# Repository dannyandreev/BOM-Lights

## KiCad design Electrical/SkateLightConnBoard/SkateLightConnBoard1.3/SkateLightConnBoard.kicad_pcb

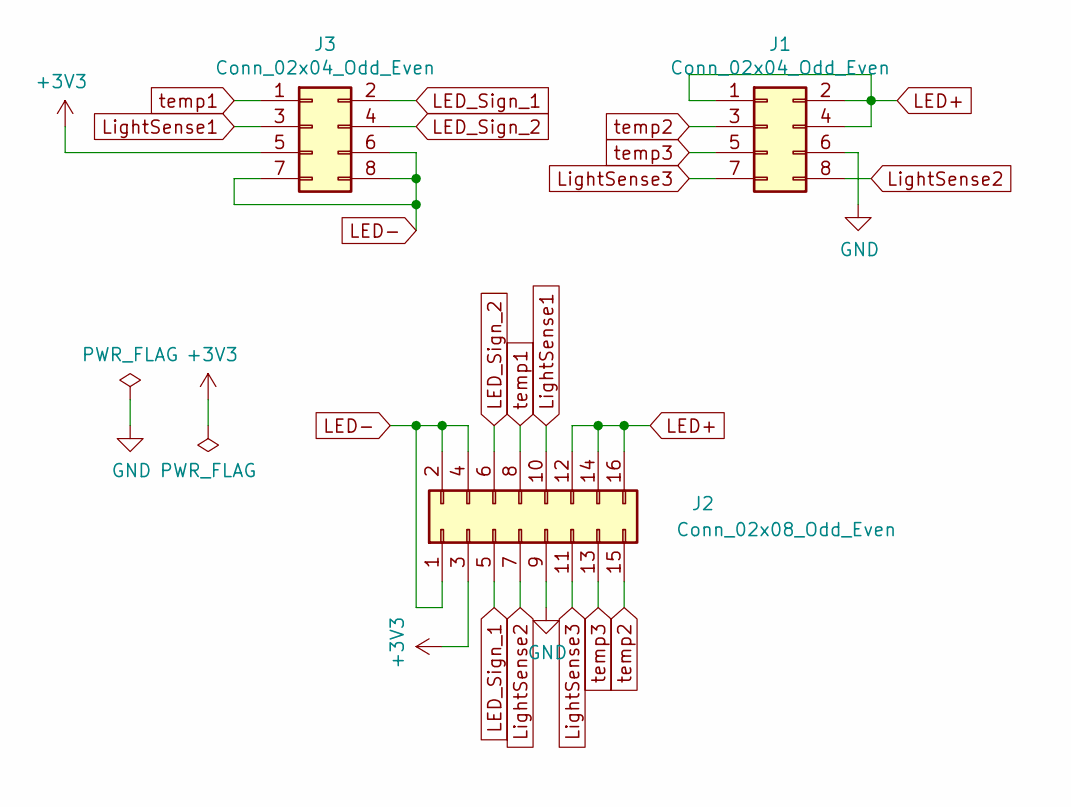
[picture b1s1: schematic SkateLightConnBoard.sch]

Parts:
J1, J3: Conn_02x04_Odd_Even; Conn_2x4_0.05in
J2: Conn_02x08_Odd_Even; Conn_2x8_0.05in

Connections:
+3V3: J2.3, J3.5
GND: J1.6, J2.9
LED+: J1.1, J1.2, J1.4, J2.12, J2.14, J2.16
LED-: J2.1, J2.2, J2.4, J3.6, J3.7, J3.8
LED_Sign_1: J2.5, J3.2
LED_Sign_2: J2.6, J3.4
LightSense1: J2.10, J3.3
LightSense2: J1.8, J2.7
LightSense3: J1.7, J2.11
temp1: J2.8, J3.1
temp2: J1.3, J2.15
temp3: J1.5, J2.13

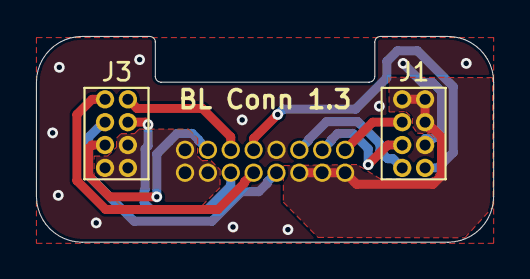
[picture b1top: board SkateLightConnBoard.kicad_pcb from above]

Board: 2 copper layers, 25.4 x 11.4 mm, 3 parts (1 on the bottom side), 12 nets.

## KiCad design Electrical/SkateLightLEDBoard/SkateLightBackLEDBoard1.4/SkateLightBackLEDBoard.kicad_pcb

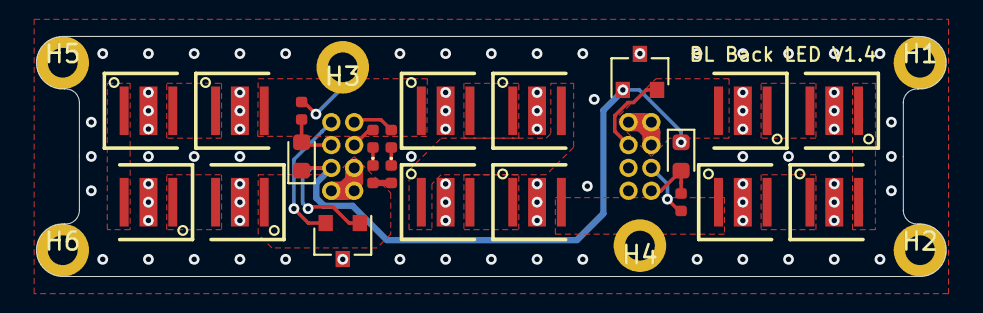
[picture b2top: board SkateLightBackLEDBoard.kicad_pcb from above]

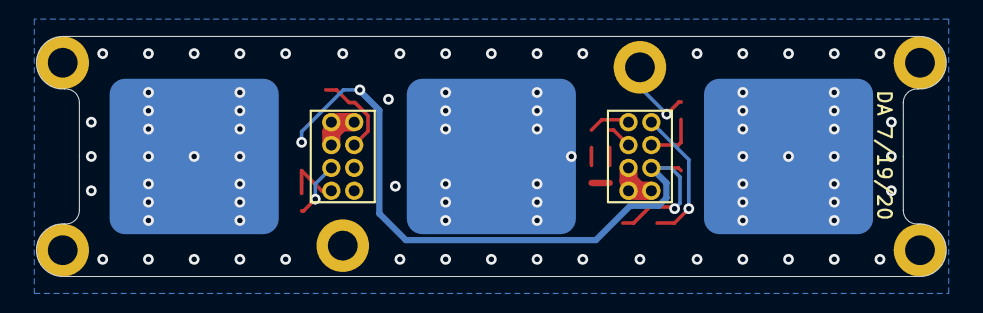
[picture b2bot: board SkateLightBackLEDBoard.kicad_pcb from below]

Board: 2 copper layers, 50.5 x 13.3 mm, 33 parts (5 on the bottom side), 23 nets.

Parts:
D1, D2, D3, D4, D5, D6, D7, D8, D9, D10, D11, D12: LED_PAD; SST-10-DR-B90-G660
D13: LEDR; D_0402_1005Metric
D14: LEDG; D_0402_1005Metric
H1, H2, H3, H4, H5, H6: MountingHole_Pad; MH_0-80_Screw_Grounded
HS1, HS2, HS3: Heatsink_Pad; BomLightBackLEDHeatsink
J1, J2: Conn_02x04_Odd_Even; Conn_2x4_0.05in
Q1, Q2: Q_Photo_NPN; D_0603_1608Metric
R1, R2: 10k 5%; R_0402_1005Metric
R3: 2k7 5%; R_0402_1005Metric
R4: 390 5%; R_0402_1005Metric
U1, U2: MCP9700AT-E_TT; SOT-23

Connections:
+3V3: J1.6, Q1.1, Q2.1, U1.1, U2.1
GND: D1.3, D2.3, D3.3, D4.3, D5.3, D6.3, D7.3, D8.3, D9.3, D10.3, D11.3, D12.3, H1.1, H2.1, H3.1, H4.1, H5.1, H6.1, HS1.1, HS2.1, HS3.1, J2.5, R1.2, R2.2, R3.2, R4.2, U1.3, U2.3
LED+: D12.2, J2.1, J2.2, J2.3
LED-: D1.1, J1.5, J1.7, J1.8
LED_Sign_1: D13.2, J1.1
LED_Sign_2: D14.2, J1.3
LightSense1: J1.4, Q1.2, R1.1
LightSense2: J2.7, Q2.2, R2.1
unnamed: D1.2, D2.1
unnamed: D2.2, D3.1
unnamed: D3.2, D4.1
unnamed: D4.2, D5.1
unnamed: D5.2, D6.1
unnamed: D6.2, D7.1
unnamed: D7.2, D8.1
unnamed: D8.2, D9.1
unnamed: D9.2, D10.1
unnamed: D10.2, D11.1
unnamed: D11.2, D12.1
unnamed: D13.1, R3.1
unnamed: D14.1, R4.1
Temp1: J1.2, U1.2
Temp2: J2.4, U2.2

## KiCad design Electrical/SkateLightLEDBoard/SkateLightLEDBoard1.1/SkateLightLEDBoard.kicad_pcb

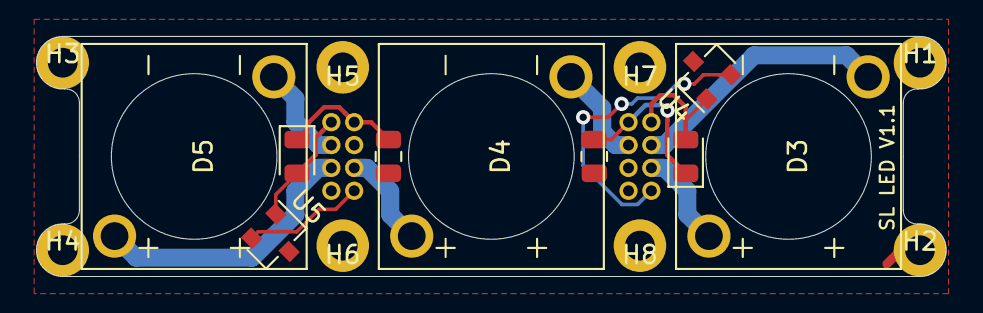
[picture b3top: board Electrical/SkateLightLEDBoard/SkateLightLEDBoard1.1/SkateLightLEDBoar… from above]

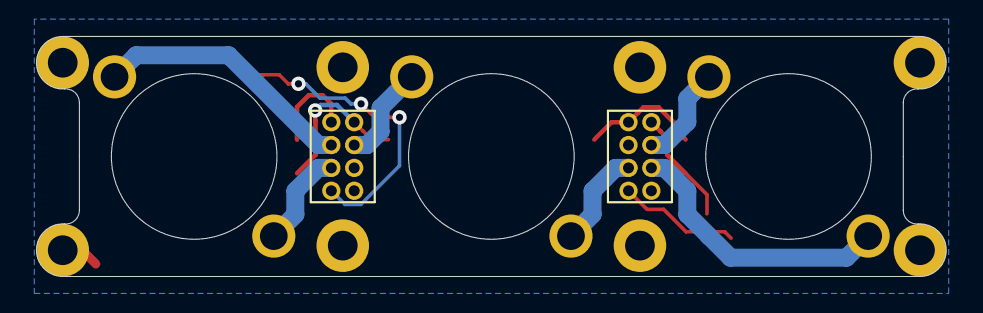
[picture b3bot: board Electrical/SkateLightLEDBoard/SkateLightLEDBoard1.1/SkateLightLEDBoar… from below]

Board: 2 copper layers, 50.5 x 13.3 mm, 19 parts (2 on the bottom side), 13 nets.

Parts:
D1, D2: D_Photo; D_0805_2012Metric
D3, D4, D5: LED; BXRE-40E0800-D-73
H1, H2, H3, H4, H5, H6, H7, H8: MountingHole_Pad; MH_0-80_Screw_Grounded
J1, J2: Conn_02x04_Odd_Even; Conn_2x4_0.05in
R1, R2: R; R_0805_2012Metric
U4, U5: MCP9700AT-E_TT; SOT-23

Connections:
3V3_1: D1.2, J1.1, U4.1
3V3_2: D2.2, J2.2, U5.1
GND: H1.1, H2.1, H3.1, H4.1, H5.1, H6.1, H7.1, H8.1, J1.8, J2.8, R1.2, R2.2, U4.3, U5.3
LED1A: D3.2, J1.3
LED1C: D3.1, J1.5
LED2A: D4.2, J1.4
LED2C: D4.1, J2.5
LED3A: D5.2, J2.4
LED3C: D5.1, J2.6
LightSense1: D1.1, J1.2, R1.1
LightSense2: D2.1, J2.1, R2.1
Temp1: J1.7, U4.2
Temp2: J2.7, U5.2

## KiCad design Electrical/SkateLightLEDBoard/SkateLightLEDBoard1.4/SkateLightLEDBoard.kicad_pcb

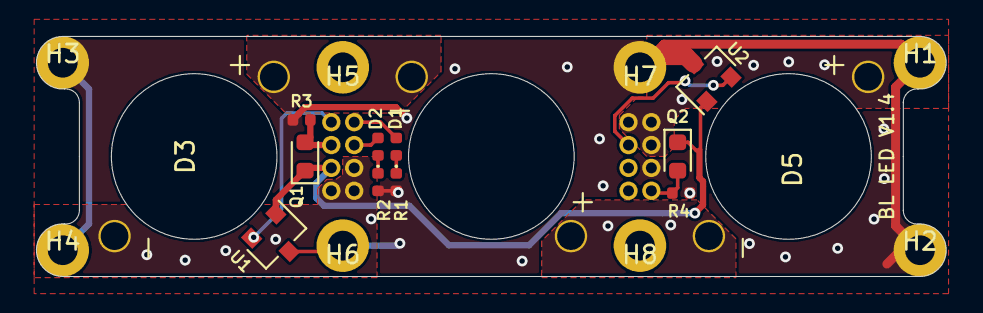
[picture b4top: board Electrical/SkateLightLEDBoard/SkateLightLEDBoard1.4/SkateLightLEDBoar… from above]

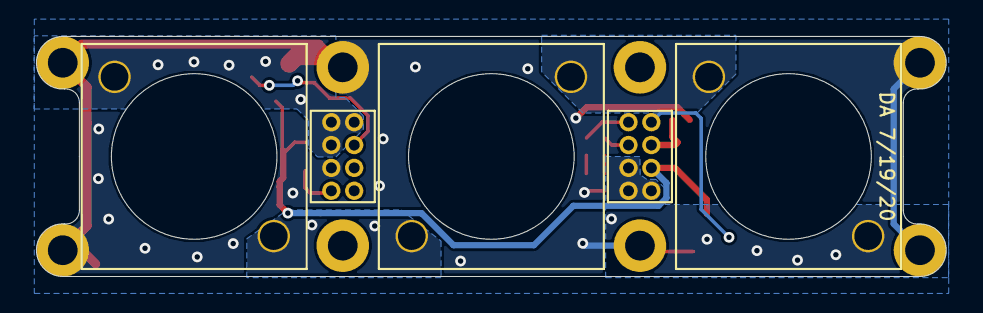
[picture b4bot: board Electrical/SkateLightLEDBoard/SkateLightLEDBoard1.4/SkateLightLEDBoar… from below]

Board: 2 copper layers, 50.5 x 13.3 mm, 23 parts (2 on the bottom side), 14 nets.

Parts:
D1: LEDR; D_0402_1005Metric
D2: LEDG; D_0402_1005Metric
D3, D4, D5: LED; BXRE-40E0800-D-73
H1, H2, H3, H4, H5, H6, H7, H8: MountingHole_Pad; MH_0-80_Screw_Grounded
J1, J2: Conn_02x04_Odd_Even; Conn_2x4_0.05in
Q1, Q2: Q_Photo_NPN; D_0603_1608Metric
R1: 2k7 5%; R_0402_1005Metric
R2: 390 5%; R_0402_1005Metric
R3, R4: 10k 1%; R_0402_1005Metric
U1, U2: MCP9700AT-E_TT; SOT-23

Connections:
+3V3: J1.6, Q1.1, Q2.1, U1.1, U2.1
GND: H1.1, H2.1, H3.1, H4.1, H6.1, H7.1, J2.5, R1.2, R2.2, R3.2, R4.2, U1.3, U2.3
LED+: D5.1, J2.1, J2.2, J2.3
LED-: D3.2, J1.5, J1.7, J1.8
LED_Sign_1: D1.2, J1.1
LED_Sign_2: D2.2, J1.3
LightSense1: J1.4, Q1.2, R3.1
LightSense2: J2.7, Q2.2, R4.1
unnamed: D1.1, R1.1
unnamed: D2.1, R2.1
unnamed: D3.1, D4.2
unnamed: D4.1, D5.2
Temp1: J1.2, U1.2
Temp2: J2.4, U2.2

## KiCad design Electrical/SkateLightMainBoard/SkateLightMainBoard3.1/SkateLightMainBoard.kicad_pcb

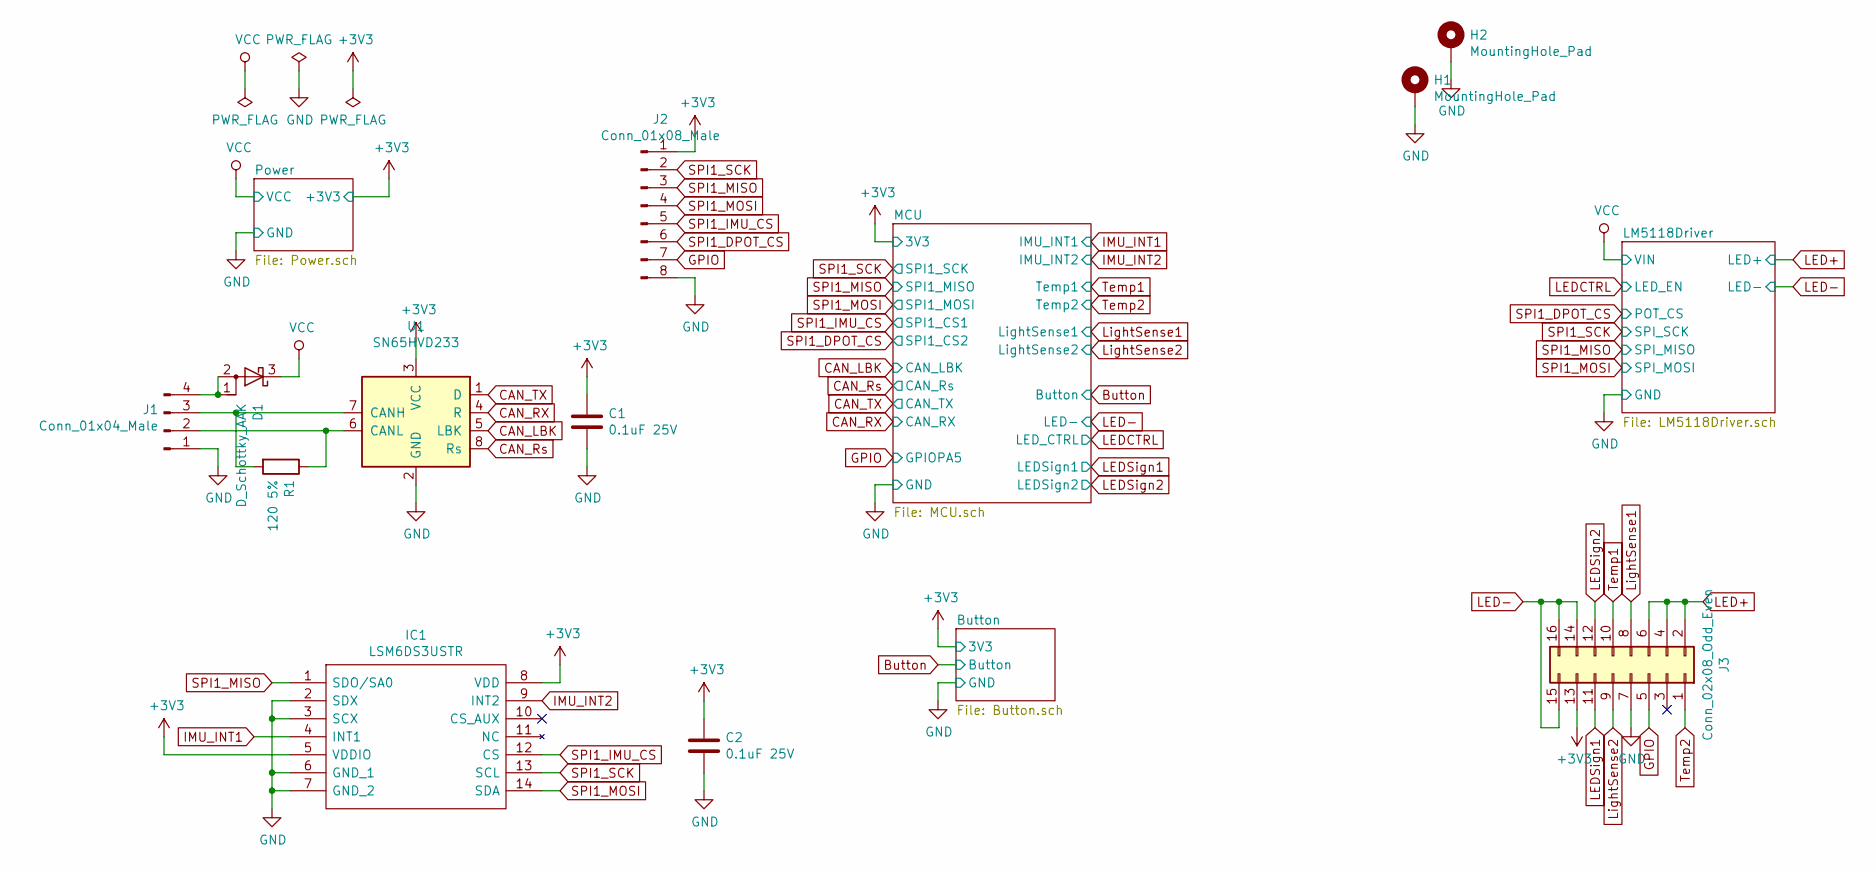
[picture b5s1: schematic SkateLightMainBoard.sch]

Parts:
C1, C2: 0.1uF 25V; C_0805_2012Metric
D1: D_Schottky_AAK; TO-277A
H1: MountingHole_Pad; ThermalPadV2_SkateLight_L
H2: MountingHole_Pad; ThermalPadV2_SkateLight_R
IC1: LSM6DS3USTR; LGA-14(2.5X3X0.86); Manufacturer_Part_Number LSM6DS3USTR; Mouser Part Number 511-LSM6DS3USTR
J1: Conn_01x04_Male; 4 Wire Pad
J2: Conn_01x08_Male; PinHeader_1x08_P2.54mm_Vertical
J3: Conn_02x08_Odd_Even; Conn_2x8_0.05in
R1: 120 5%; R_0805_2012Metric
U1: SN65HVD233; SOIC-8_3.9x4.9mm_P1.27mm

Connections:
+3V3: C1.1, C2.1, IC1.5 (VDDIO), IC1.8 (VDD), J2.1, J3.13, U1.3 (VCC); also elsewhere on the board
CAN_LBK: U1.5 (LBK); also elsewhere on the board
CAN_RX: U1.4 (R); also elsewhere on the board
CAN_Rs: U1.8 (Rs); also elsewhere on the board
CAN_TX: U1.1 (D); also elsewhere on the board
GND: C1.2, C2.2, H1.1, H2.1, IC1.2 (SDX), IC1.3 (SCX), IC1.6 (GND_1), IC1.7 (GND_2), J1.1, J2.8, J3.7, U1.2 (GND); also elsewhere on the board
GPIO: J2.7, J3.5; also elsewhere on the board
IMU_INT1: IC1.4 (INT1); also elsewhere on the board
IMU_INT2: IC1.9 (INT2); also elsewhere on the board
LED+: J3.2, J3.4, J3.6; also elsewhere on the board
LED-: J3.14, J3.15, J3.16; also elsewhere on the board
LEDSign1: J3.11; also elsewhere on the board
LEDSign2: J3.12; also elsewhere on the board
LightSense1: J3.8; also elsewhere on the board
LightSense2: J3.9; also elsewhere on the board
unnamed: D1.1 (A), D1.2 (A), J1.4
unnamed: J1.2, R1.1, U1.6 (CANL)
unnamed: J1.3, R1.2, U1.7 (CANH)
SPI1_DPOT_CS: J2.6; also elsewhere on the board
SPI1_IMU_CS: IC1.12 (CS), J2.5; also elsewhere on the board
SPI1_MISO: IC1.1 (SDO/SA0), J2.3; also elsewhere on the board
SPI1_MOSI: IC1.14 (SDA), J2.4; also elsewhere on the board
SPI1_SCK: IC1.13 (SCL), J2.2; also elsewhere on the board
Temp1: J3.10; also elsewhere on the board
Temp2: J3.1; also elsewhere on the board
VCC: D1.3 (K); also elsewhere on the board

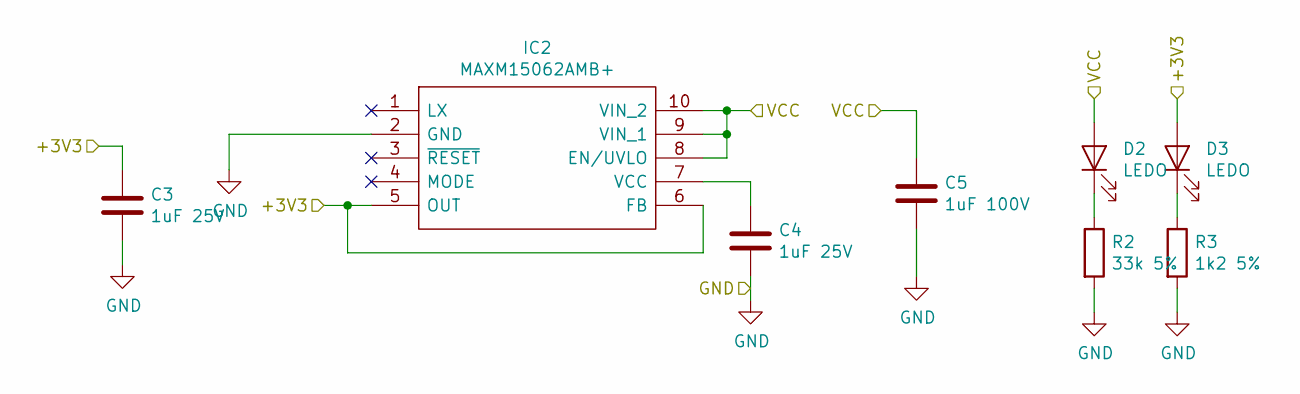
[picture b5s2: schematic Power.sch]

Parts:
C3, C4: 1uF 25V; C_0805_2012Metric
C5: 1uF 100V; C_0805_2012Metric
D2, D3: LEDO; LED_0805_2012Metric
IC2: MAXM15062AMB+; MAXM15462AMB; Manufacturer_Part_Number MAXM15062AMB+; Mouser Part Number 700-MAXM15062AMB+
R2: 33k 5%; R_0805_2012Metric
R3: 1k2 5%; R_0805_2012Metric

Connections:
+3V3: C3.1, D3.2 (A), IC2.5 (OUT), IC2.6 (FB); also elsewhere on the board
GND: C3.2, C4.2, C5.2, IC2.2 (GND), R2.2, R3.2; also elsewhere on the board
unnamed: C4.1, IC2.7 (VCC)
unnamed: D2.1 (K), R2.1
unnamed: D3.1 (K), R3.1
VCC: C5.1, D2.2 (A), IC2.8 (EN/UVLO), IC2.9 (VIN_1), IC2.10 (VIN_2); also elsewhere on the board

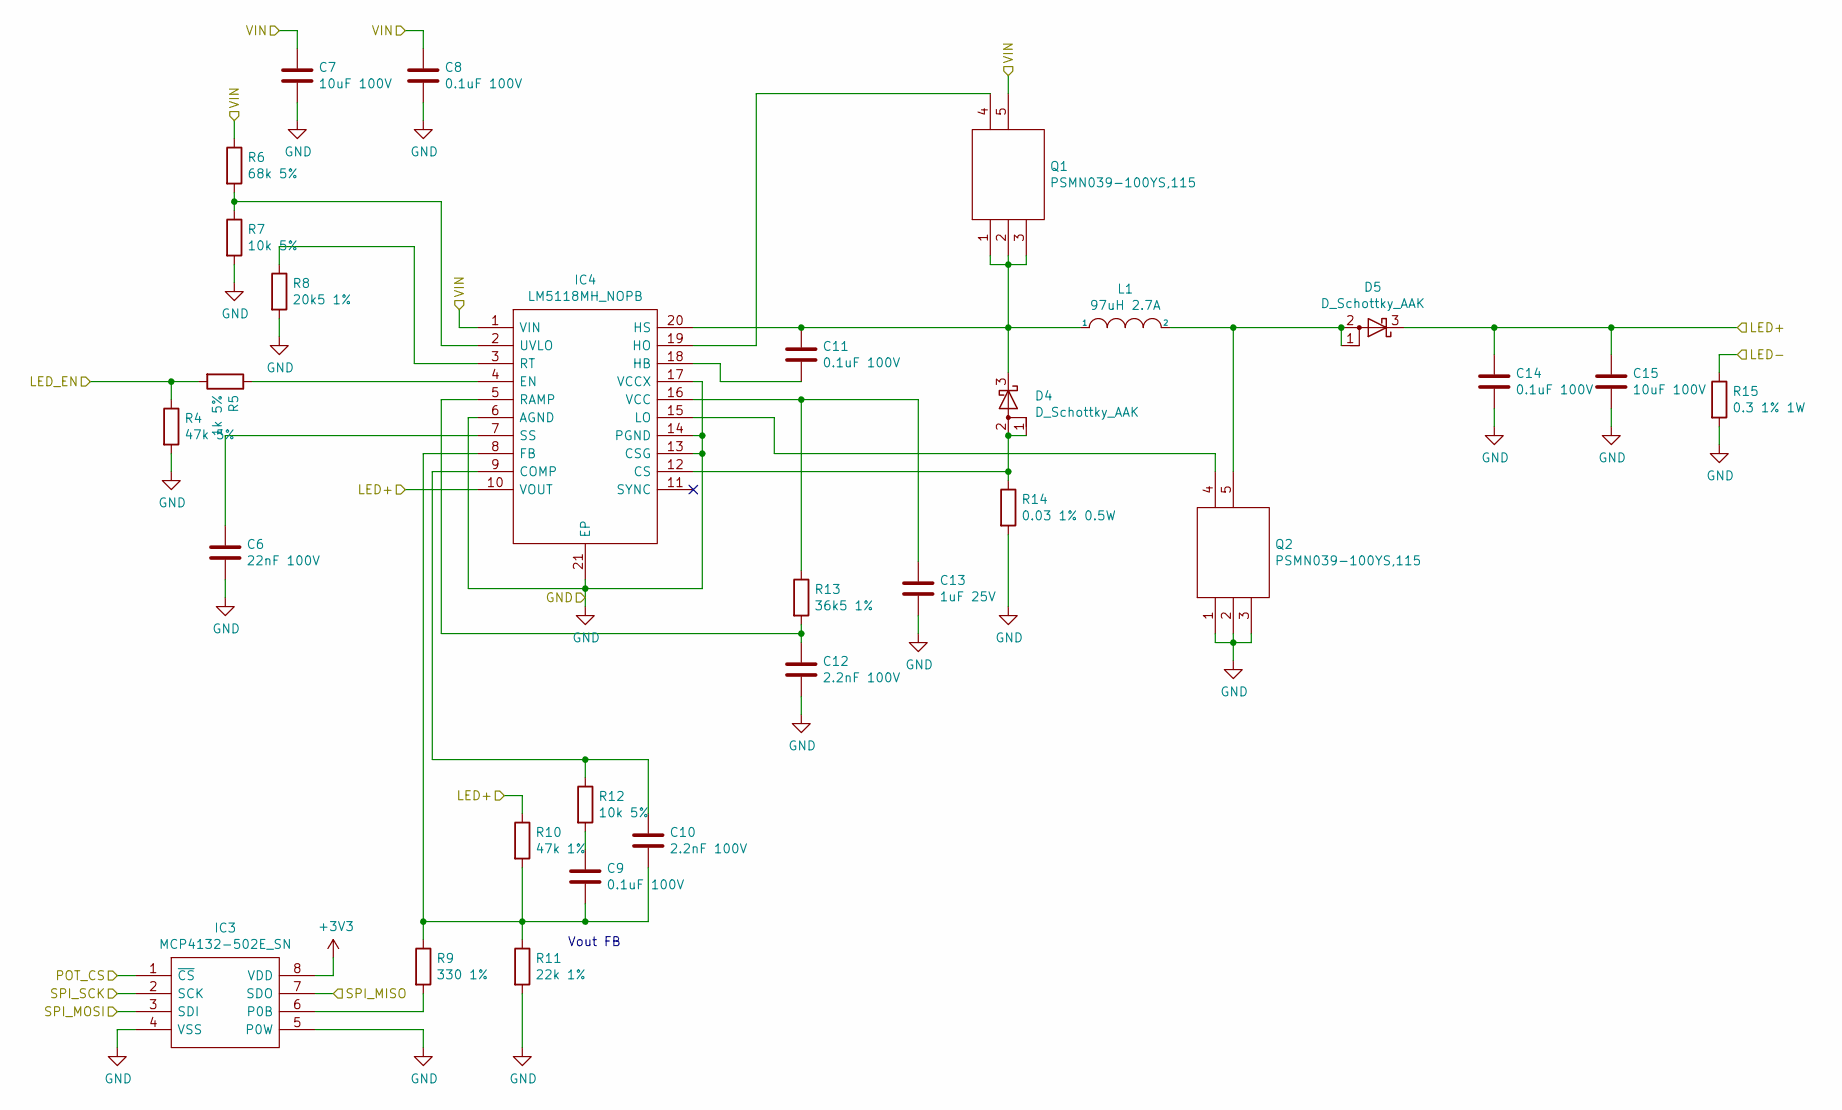
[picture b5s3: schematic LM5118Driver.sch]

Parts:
C6: 22nF 100V; C_0805_2012Metric
C7, C15: 10uF 100V; C_1210_3225Metric
C8, C9, C11, C14: 0.1uF 100V; C_0805_2012Metric
C10, C12: 2.2nF 100V; C_0805_2012Metric
C13: 1uF 25V; C_0805_2012Metric
D4, D5: D_Schottky_AAK; TO-277A
IC3: MCP4132-502E_SN; TSSOP-8_3x3mm_P0.65mm; Manufacturer_Part_Number MCP4132-502E/SN; Mouser Part Number 579-MCP4132-502E/SN
IC4: LM5118MH_NOPB; SOP65P640X110-21N; Manufacturer_Part_Number LM5118MH/NOPB; Mouser Part Number 926-LM5118MH/NOPB
L1: 97uH 2.7A; ‎ETQ-P5M101YGC‎ Inductor
Q1, Q2: PSMN039-100YS,115; PSMN5R660YLX; Manufacturer_Part_Number PSMN039-100YS,115; Mouser Part Number 771-PSMN039-100YS115
R4: 47k 5%; R_0805_2012Metric
R5: 1k 5%; R_0805_2012Metric
R6: 68k 5%; R_0805_2012Metric
R7, R12: 10k 5%; R_0805_2012Metric
R8: 20k5 1%; R_0805_2012Metric
R9: 330 1%; R_0805_2012Metric
R10: 47k 1%; R_0805_2012Metric
R11: 22k 1%; R_0805_2012Metric
R13: 36k5 1%; R_0805_2012Metric
R14: 0.03 1% 0.5W; R_1206_3216Metric
R15: 0.3 1% 1W; R_2512_6332Metric

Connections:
+3V3: IC3.8 (VDD); also elsewhere on the board
GND: C6.2, C7.2, C8.2, C12.2, C13.2, C14.2, C15.2, IC3.4 (VSS), IC3.5 (P0W), IC4.6 (AGND), IC4.13 (CSG), IC4.14 (PGND), IC4.17 (VCCX), IC4.21 (EP), Q2.1, Q2.2, Q2.3, R4.2, R7.2, R8.2, R11.2, R14.2, R15.2; also elsewhere on the board
LED+: C14.1, C15.1, D5.3 (K), IC4.10 (VOUT), R10.1; also elsewhere on the board
LED-: R15.1; also elsewhere on the board
LEDCTRL: R4.1, R5.2; also elsewhere on the board
unnamed: C6.1, IC4.7 (SS)
unnamed: C9.1, R12.2
unnamed: C10.1, IC4.9 (COMP), R12.1
unnamed: C9.2, C10.2, IC4.8 (FB), R9.1, R10.2, R11.1
unnamed: C11.1, D4.3 (K), IC4.20 (HS), L1.1, Q1.1, Q1.2, Q1.3
unnamed: C11.2, IC4.18 (HB)
unnamed: C12.1, IC4.5 (RAMP), R13.2
unnamed: C13.1, IC4.16 (VCC), R13.1
unnamed: D4.1 (A), D4.2 (A), IC4.12 (CS), R14.1
unnamed: D5.1 (A), D5.2 (A), L1.2, Q2.5
unnamed: IC3.6 (P0B), R9.2
unnamed: IC4.2 (UVLO), R6.2, R7.1
unnamed: IC4.3 (RT), R8.1
unnamed: IC4.4 (EN), R5.1
unnamed: IC4.15 (LO), Q2.4
unnamed: IC4.19 (HO), Q1.4
SPI1_DPOT_CS: IC3.1 (~CS); also elsewhere on the board
SPI1_MISO: IC3.7 (SDO); also elsewhere on the board
SPI1_MOSI: IC3.3 (SDI); also elsewhere on the board
SPI1_SCK: IC3.2 (SCK); also elsewhere on the board
VCC: C7.1, C8.1, IC4.1 (VIN), Q1.5, R6.1; also elsewhere on the board

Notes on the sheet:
Vout FB

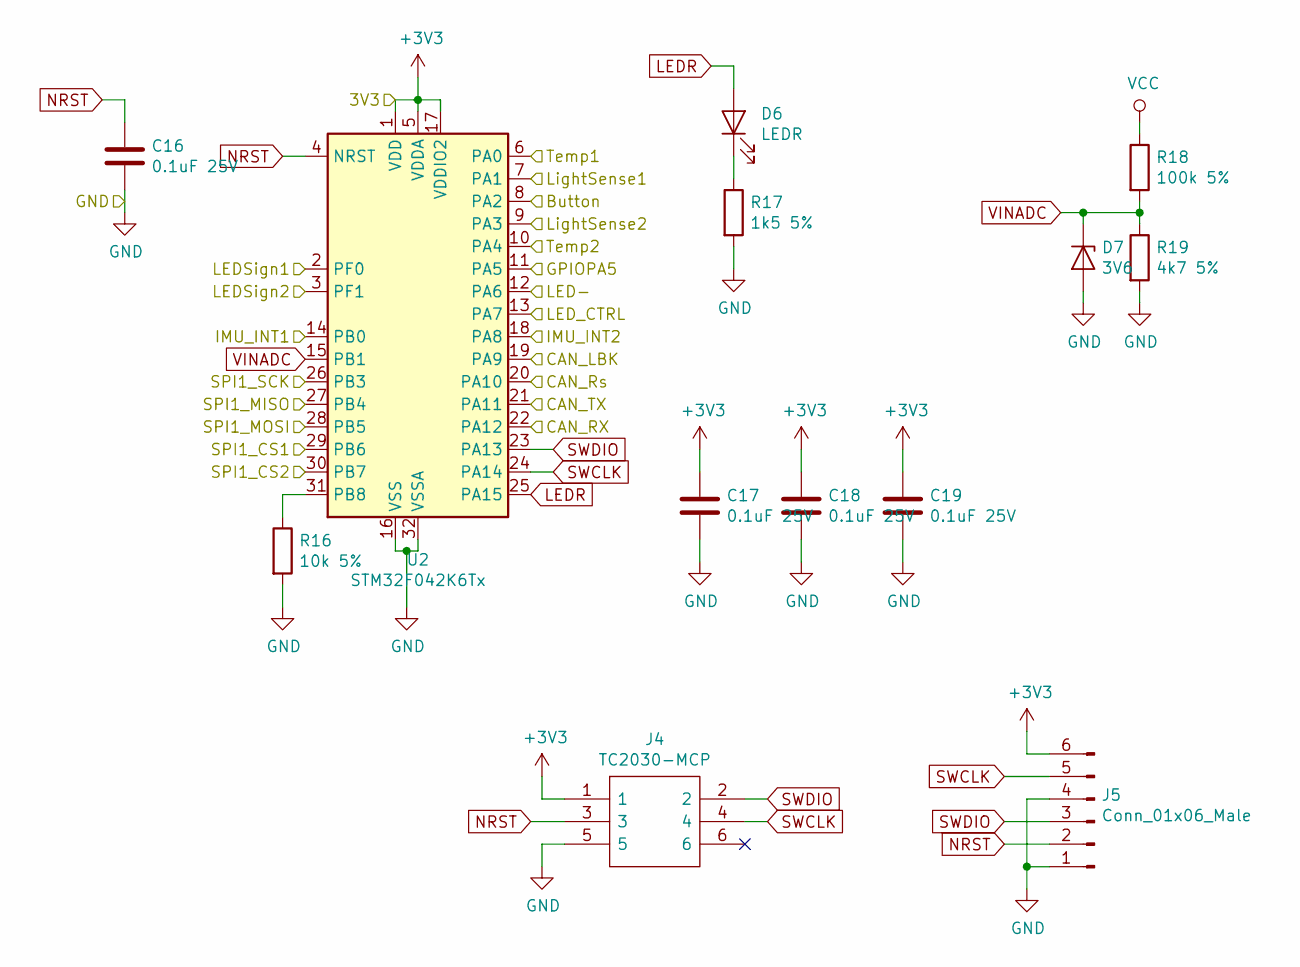
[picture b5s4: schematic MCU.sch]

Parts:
C16, C17, C18, C19: 0.1uF 25V; C_0805_2012Metric
D6: LEDR; LED_0805_2012Metric
D7: 3V6; D_SOD-323
J4: TC2030-MCP; TC2030MCP; Manufacturer_Part_Number TC2030-MCP; Mouser Part Number 579-TC2030-MCP
J5: Conn_01x06_Male; JST_PH_B6B-PH-K_1x06_P2.00mm_Vertical
R16: 10k 5%; R_0805_2012Metric
R17: 1k5 5%; R_0805_2012Metric
R18: 100k 5%; R_0805_2012Metric
R19: 4k7 5%; R_0805_2012Metric
U2: STM32F042K6Tx; LQFP-32_7x7mm_P0.8mm

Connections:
+3V3: C17.1, C18.1, C19.1, J4.1, J5.6, U2.1 (VDD), U2.5 (VDDA), U2.17 (VDDIO2); also elsewhere on the board
Button: U2.8 (PA2); also elsewhere on the board
CAN_LBK: U2.19 (PA9); also elsewhere on the board
CAN_RX: U2.22 (PA12); also elsewhere on the board
CAN_Rs: U2.20 (PA10); also elsewhere on the board
CAN_TX: U2.21 (PA11); also elsewhere on the board
GND: C16.2, C17.2, C18.2, C19.2, D7.2 (A), J4.5, J5.1, J5.4, R16.2, R17.2, R19.2, U2.16 (VSS), U2.32 (VSSA); also elsewhere on the board
GPIO: U2.11 (PA5); also elsewhere on the board
IMU_INT1: U2.14 (PB0); also elsewhere on the board
IMU_INT2: U2.18 (PA8); also elsewhere on the board
LED-: U2.12 (PA6); also elsewhere on the board
LEDCTRL: U2.13 (PA7); also elsewhere on the board
LEDR: D6.2 (A), U2.25 (PA15)
LEDSign1: U2.2 (PF0); also elsewhere on the board
LEDSign2: U2.3 (PF1); also elsewhere on the board
LightSense1: U2.7 (PA1); also elsewhere on the board
LightSense2: U2.9 (PA3); also elsewhere on the board
NRST: C16.1, J4.3, J5.2, U2.4 (NRST)
unnamed: D6.1 (K), R17.1
unnamed: R16.1, U2.31 (PB8)
SPI1_DPOT_CS: U2.30 (PB7); also elsewhere on the board
SPI1_IMU_CS: U2.29 (PB6); also elsewhere on the board
SPI1_MISO: U2.27 (PB4); also elsewhere on the board
SPI1_MOSI: U2.28 (PB5); also elsewhere on the board
SPI1_SCK: U2.26 (PB3); also elsewhere on the board
SWCLK: J4.4, J5.5, U2.24 (PA14)
SWDIO: J4.2, J5.3, U2.23 (PA13)
Temp1: U2.6 (PA0); also elsewhere on the board
Temp2: U2.10 (PA4); also elsewhere on the board
VCC: R18.1; also elsewhere on the board
VINADC: D7.1 (K), R18.2, R19.1, U2.15 (PB1)

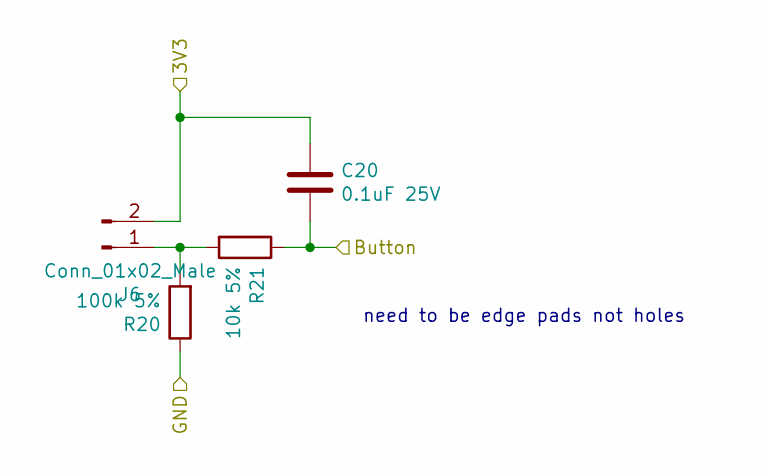
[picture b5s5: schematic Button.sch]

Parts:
C20: 0.1uF 25V; C_0805_2012Metric
J6: Conn_01x02_Male; 2WirePad
R20: 100k 5%; R_0805_2012Metric
R21: 10k 5%; R_0805_2012Metric

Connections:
+3V3: C20.1, J6.2; also elsewhere on the board
Button: C20.2, R21.1; also elsewhere on the board
GND: R20.1; also elsewhere on the board
unnamed: J6.1, R20.2, R21.2

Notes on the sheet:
need to be edge pads not holes

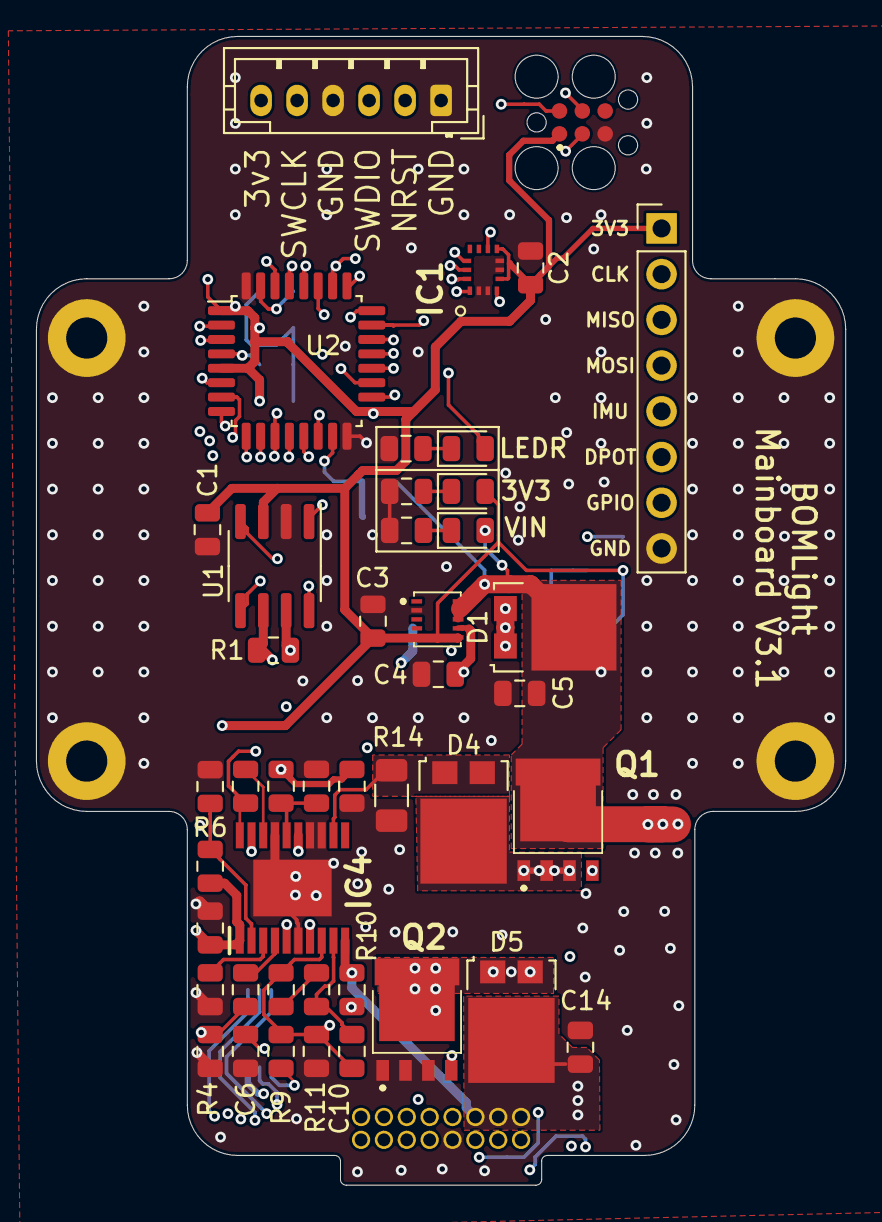
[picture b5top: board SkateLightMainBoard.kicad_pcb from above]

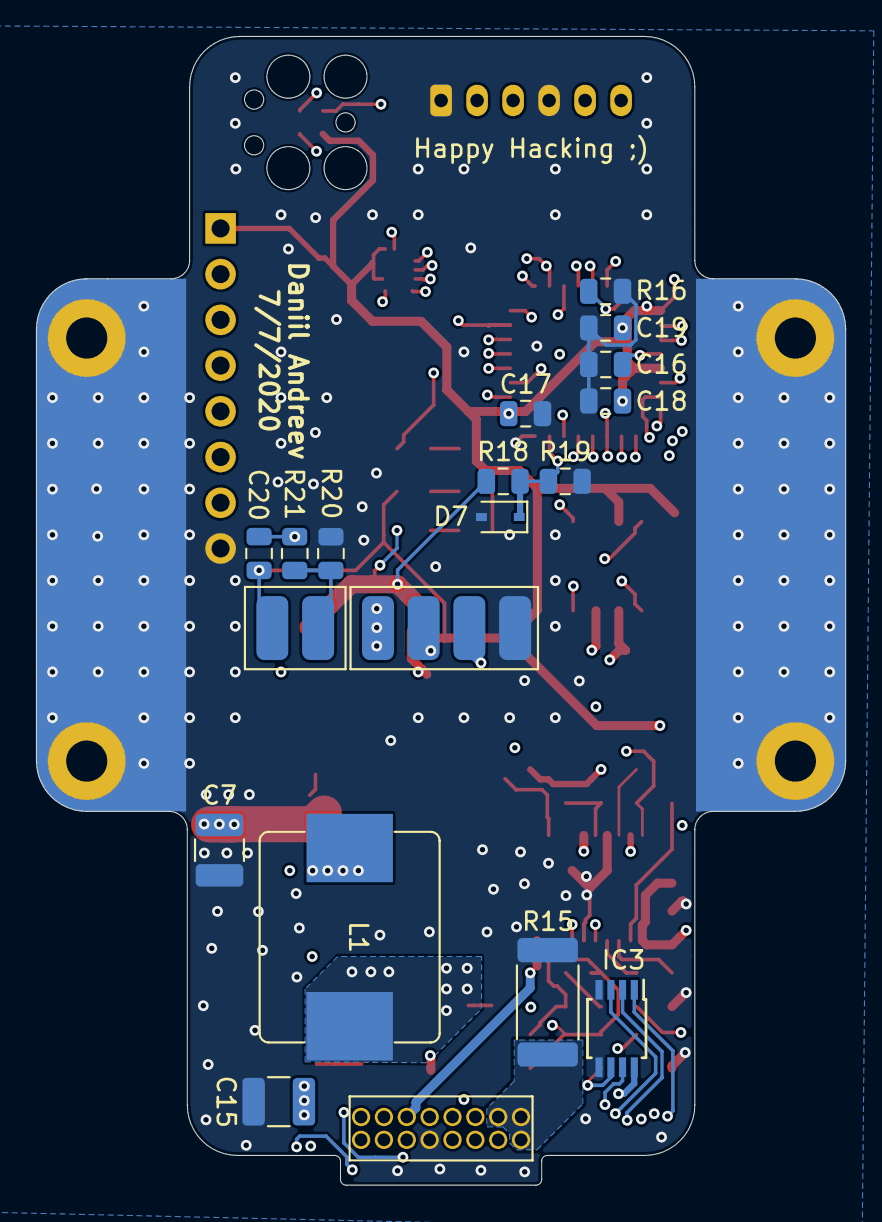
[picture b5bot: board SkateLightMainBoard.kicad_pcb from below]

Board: 4 copper layers, 45.0 x 63.8 mm, 65 parts (19 on the bottom side), 55 nets.
